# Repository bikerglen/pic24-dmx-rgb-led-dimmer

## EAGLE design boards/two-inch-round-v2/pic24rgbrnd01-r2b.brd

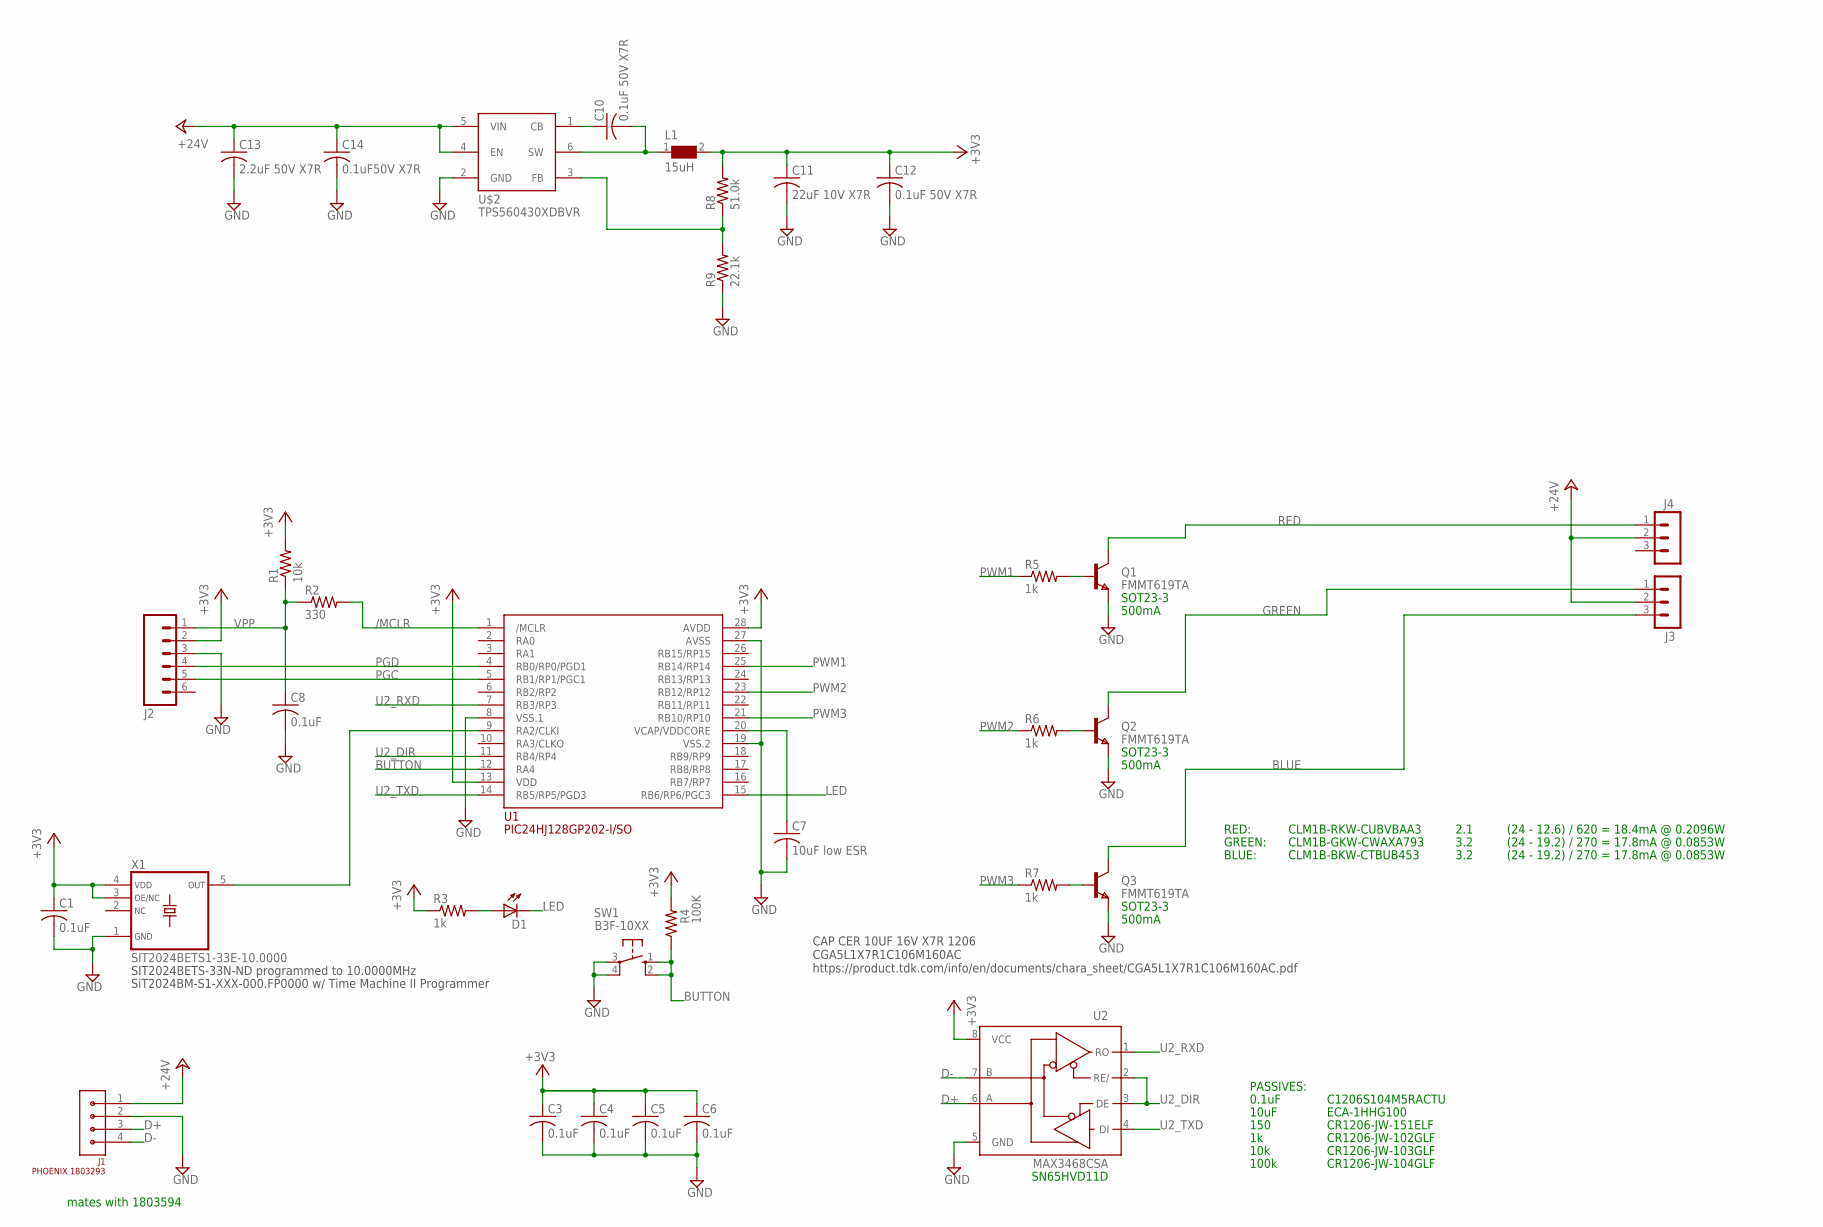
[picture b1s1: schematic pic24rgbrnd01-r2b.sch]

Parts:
C1, C3, C4, C5, C6, C8: 0.1uF; C0805
C7: 10uF low ESR; C1206
C10, C12: 0.1uF 50V X7R; C0805
C11: 22uF 10V X7R; C1206K; MFR_PART_NO C1206C226K8RAC7800
C13: 2.2uF 50V X7R; C1210K; MFR_PART_NO C1210C106K5RACTU
C14: 0.1uF50V X7R; C0805
D1: LED3MM
J1: PHOENIX 1803293; CON-PHOENIX-1803293-3.81-1X4
J2: M06SIP; 1X06
J3, J4: MA03-1
L1: 15uH; WE-SPC_48XX
Q1, Q2, Q3: FMMT619TA; SOT-23
R1: 10k; R0805
R2: 330; R0805
R3, R5, R6, R7: 1k; R0805
R4: 100K; R0805
R8: 51.0k; R0805
R9: 22.1k; R0805
SW1: B3F-10XX
U1: PIC24HJ128GP202-I/SO; SO28W
U2: MAX3468CSA; SO08
U$2: TPS560430XDBVR; SOT23-6
X1: SIT2024BETS1-33E-10.0000; SOT23-5

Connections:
+3V3: C1.1, C3.1, C4.1, C5.1, C6.1, C11.1, C12.1, J2.2, L1.2, R1.2, R3.1, R4.2, R8.2, U1.13 (VDD), U1.28 (AVDD), U2.8 (VCC), X1.3 (OE/NC), X1.4 (VDD)
+24V: C13.1, C14.1, J1.1, J3.2, J4.2, U$2.4 (EN), U$2.5 (VIN)
/MCLR: R2.2, U1.1 (/MCLR)
BLUE: J3.3, Q3.1 (C)
BUTTON: R4.1, SW1.1 (S), SW1.2 (S1), U1.12 (RA4)
CB: C10.1, U$2.1 (CB)
D+: J1.3, U2.6 (A)
D-: J1.4, U2.7 (B)
FB: R8.1, R9.2, U$2.3 (FB)
GND: C1.2, C3.2, C4.2, C5.2, C6.2, C7.2, C8.2, C11.2, C12.2, C13.2, C14.2, J1.2, J2.3, Q1.2 (E), Q2.2 (E), Q3.2 (E), R9.1, SW1.3, SW1.4 (P1), U1.8 (VSS.1), U1.19 (VSS.2), U1.27 (AVSS), U2.5 (GND), U$2.2 (GND), X1.1 (GND)
GREEN: J3.1, Q2.1 (C)
LED: D1.K (C), U1.15 (RB6/RP6/PGC3)
unnamed: C7.1, U1.20 (VCAP/VDDCORE)
unnamed: U1.9 (RA2/CLKI), X1.5 (OUT)
unnamed: Q1.3 (B), R5.2
unnamed: Q2.3 (B), R6.2
unnamed: Q3.3 (B), R7.2
unnamed: D1.A, R3.2
PGC: J2.5, U1.5 (RB1/RP1/PGC1)
PGD: J2.4, U1.4 (RB0/RP0/PGD1)
PWM1: R5.1, U1.25 (RB14/RP14)
PWM2: R6.1, U1.23 (RB12/RP12)
PWM3: R7.1, U1.21 (RB10/RP10)
RED: J4.1, Q1.1 (C)
SW: C10.2, L1.1, U$2.6 (SW)
U2_DIR: U1.11 (RB4/RP4), U2.2 (RE/), U2.3 (DE)
U2_RXD: U1.7 (RB3/RP3), U2.1 (RO)
U2_TXD: U1.14 (RB5/RP5/PGD3), U2.4 (DI)
VPP: C8.1, J2.1, R1.1, R2.1

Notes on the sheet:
SN65HVD11D
0.1uF
C1206S104M5RACTU
150
10k
100k
CR1206-JW-102GLF
CR1206-JW-151ELF
CR1206-JW-104GLF
CR1206-JW-103GLF
PASSIVES:
10uF
ECA-1HHG100
SOT23-3
500mA
RED:
CLM1B-RKW-CUBVBAA3
2.1
GREEN:
CLM1B-GKW-CWAXA793
3.2
BLUE:
CLM1B-BKW-CTBUB453
(24 - 12.6) / 620 = 18.4mA @ 0.2096W
(24 - 19.2) / 270 = 17.8mA @ 0.0853W
mates with 1803594
CAP CER 10UF 16V X7R 1206 CGA5L1X7R1C106M160AC https://product.tdk.com/info/en/documents/chara_sheet/CGA5L1X7R1C106M160AC.pdf
SIT2024BETS-33N-ND programmed to 10.0000MHz
SiT2024BM-S1-XXX-000.FP0000 w/ Time Machine II Programmer

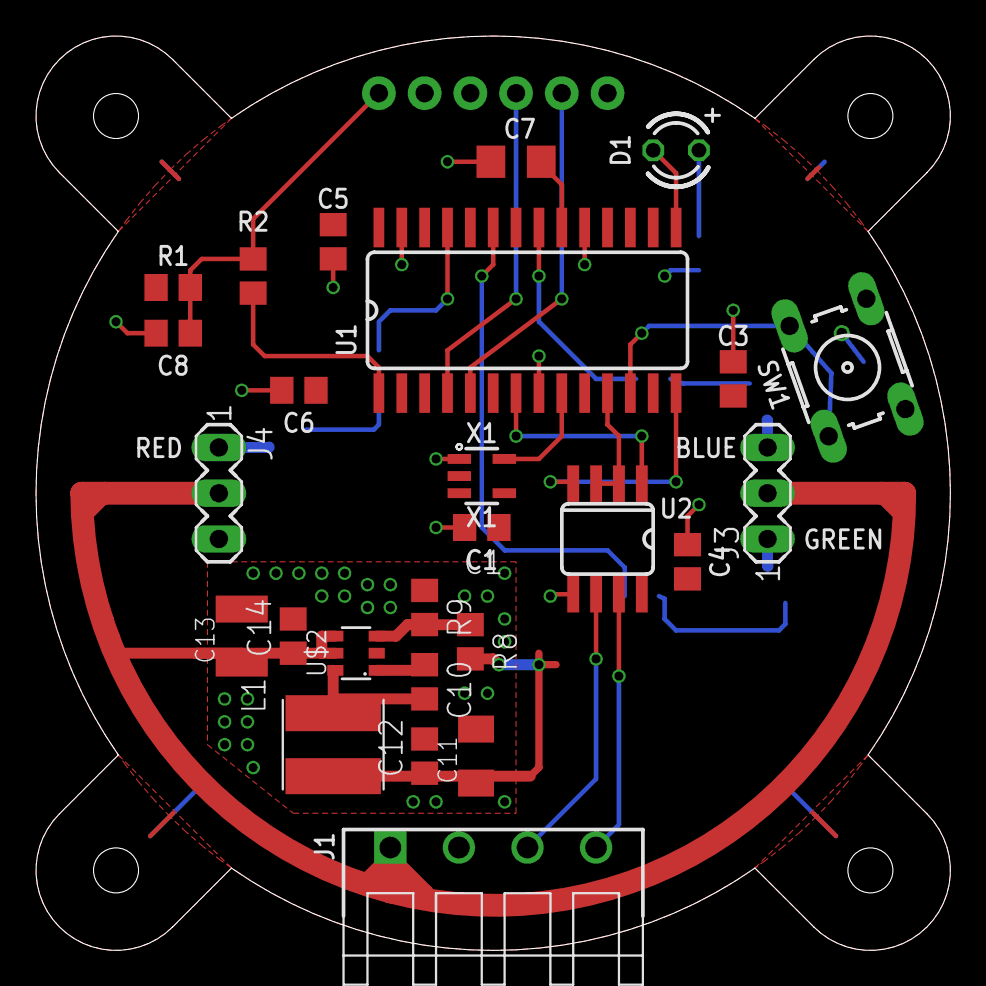
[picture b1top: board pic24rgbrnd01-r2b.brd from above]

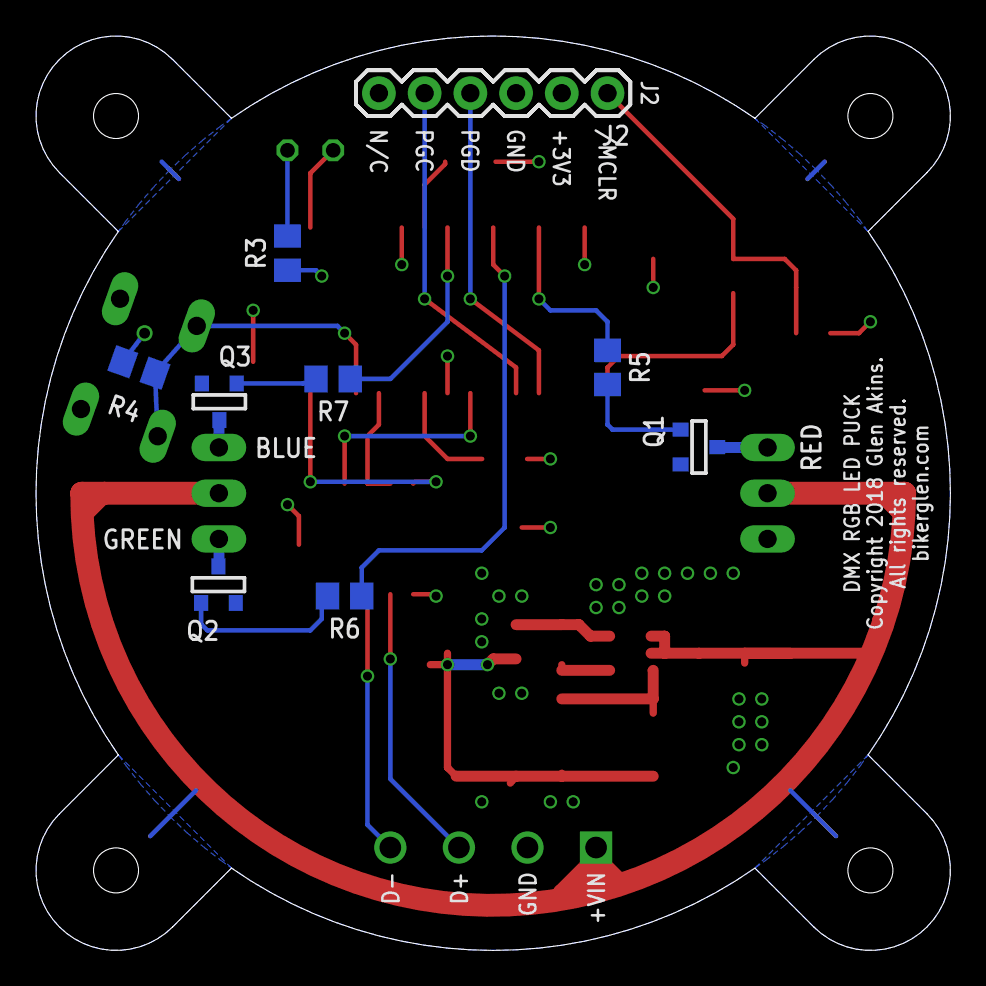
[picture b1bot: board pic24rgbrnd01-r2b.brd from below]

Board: 2 copper layers, 50.8 x 50.8 mm, 35 parts (9 on the bottom side), 29 nets.

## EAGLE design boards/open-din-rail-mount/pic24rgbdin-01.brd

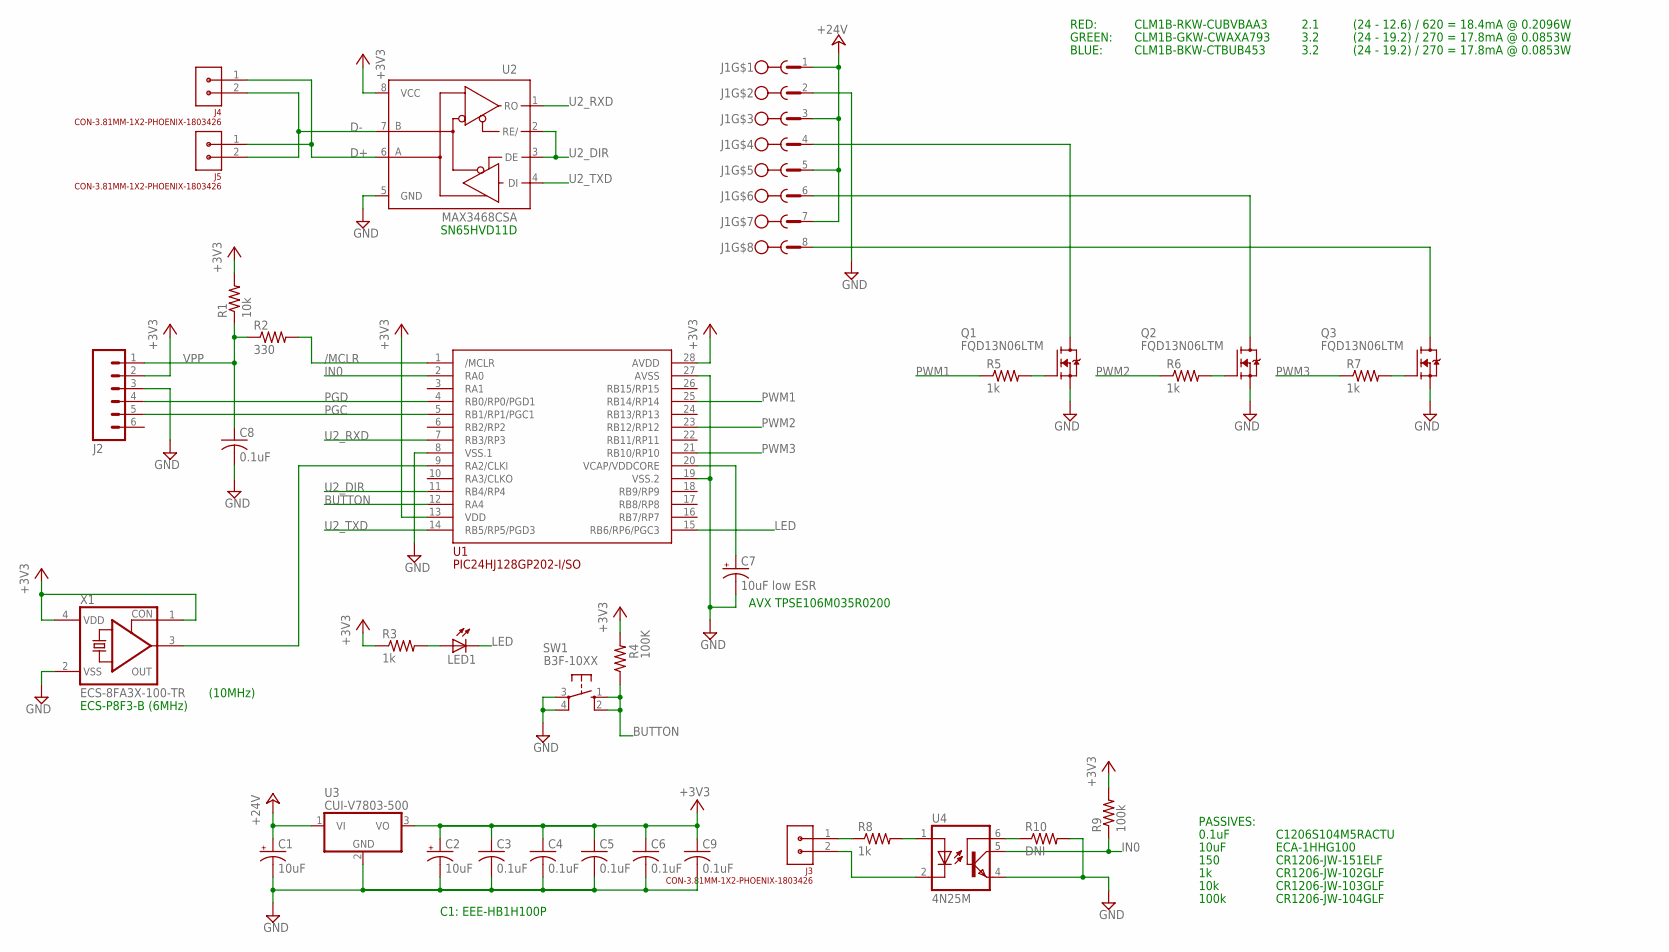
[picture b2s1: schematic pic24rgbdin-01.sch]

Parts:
C1, C2: 10uF; PANASONIC_D
C3, C4, C5, C6, C8, C9: 0.1uF; C1206
C7: 10uF low ESR; D/7343-31R
J1: CON-3.81MM-1X8-PHOENIX-HEADER-1803484; CON-PHOENIX-1803484-3.81-1X8
J2: M06SIP; 1X06
J3, J4, J5: CON-3.81MM-1X2-PHOENIX-1803426; CON-PHOENIX-1803426-3.81-1X2
LED1: LED3MM
Q1, Q2, Q3: FQD13N06LTM; TO252-D-PAK-FQD13N06LTM
R1: 10k; R1206
R2: 330; R1206
R3, R5, R6, R7, R8: 1k; R1206
R4: 100K; M1206
R9: 100k; R1206
R10: DNI; R1206
SW1: B3F-10XX
U1: PIC24HJ128GP202-I/SO; SO28W
U2: MAX3468CSA; SO08
U3: CUI-V7803-500; CUI-78XX-500
U4: 4N25M; DIL06
X1: ECS-8FA3X-100-TR; 1100S

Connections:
+3V3: C2.+, C3.1, C4.1, C5.1, C6.1, C9.1, J2.2, R1.2, R3.1, R4.2, R9.2, U1.13 (VDD), U1.28 (AVDD), U2.8 (VCC), U3.3 (VO), X1.1 (CON), X1.4 (VDD)
+24V: C1.+, J1.1, J1.3, J1.5, J1.7, U3.1 (VI)
/MCLR: R2.2, U1.1 (/MCLR)
BLUE: J1.8, Q3.P$4 (D)
BUTTON: R4.1, SW1.1 (S), SW1.2 (S1), U1.12 (RA4)
D+: J4.1, J5.1, U2.6 (A)
D-: J4.2, J5.2, U2.7 (B)
GND: C1.-, C2.-, C3.2, C4.2, C5.2, C6.2, C7.-, C8.2, C9.2, J1.2, J2.3, Q1.P$3 (S), Q2.P$3 (S), Q3.P$3 (S), R10.2, SW1.3, SW1.4 (P1), U1.8 (VSS.1), U1.19 (VSS.2), U1.27 (AVSS), U2.5 (GND), U3.2 (GND), U4.4 (EMI), X1.2 (VSS)
GREEN: J1.6, Q2.P$4 (D)
IN0: R9.1, U1.2 (RA0), U4.5 (COL)
LED: LED1.K (C), U1.15 (RB6/RP6/PGC3)
unnamed: Q2.P$1 (G), R6.2
unnamed: Q3.P$1 (G), R7.2
unnamed: R8.2, U4.1 (A)
unnamed: C7.+, U1.20 (VCAP/VDDCORE)
unnamed: U1.9 (RA2/CLKI), X1.3 (OUT)
unnamed: R10.1, U4.6 (BAS)
unnamed: J3.2, U4.2 (C)
unnamed: J3.1, R8.1
unnamed: Q1.P$1 (G), R5.2
unnamed: LED1.A, R3.2
PGC: J2.5, U1.5 (RB1/RP1/PGC1)
PGD: J2.4, U1.4 (RB0/RP0/PGD1)
PWM1: R5.1, U1.25 (RB14/RP14)
PWM2: R6.1, U1.23 (RB12/RP12)
PWM3: R7.1, U1.21 (RB10/RP10)
RED: J1.4, Q1.P$4 (D)
U2_DIR: U1.11 (RB4/RP4), U2.2 (RE/), U2.3 (DE)
U2_RXD: U1.7 (RB3/RP3), U2.1 (RO)
U2_TXD: U1.14 (RB5/RP5/PGD3), U2.4 (DI)
VPP: C8.1, J2.1, R1.1, R2.1

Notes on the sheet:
(10MHz)
ECS-P8F3-B (6MHz)
SN65HVD11D
C1: EEE-HB1H100P
0.1uF
C1206S104M5RACTU
150
10k
100k
CR1206-JW-102GLF
CR1206-JW-151ELF
CR1206-JW-104GLF
CR1206-JW-103GLF
PASSIVES:
10uF
ECA-1HHG100
RED:
CLM1B-RKW-CUBVBAA3
2.1
GREEN:
CLM1B-GKW-CWAXA793
3.2
BLUE:
CLM1B-BKW-CTBUB453
(24 - 12.6) / 620 = 18.4mA @ 0.2096W
(24 - 19.2) / 270 = 17.8mA @ 0.0853W
AVX TPSE106M035R0200

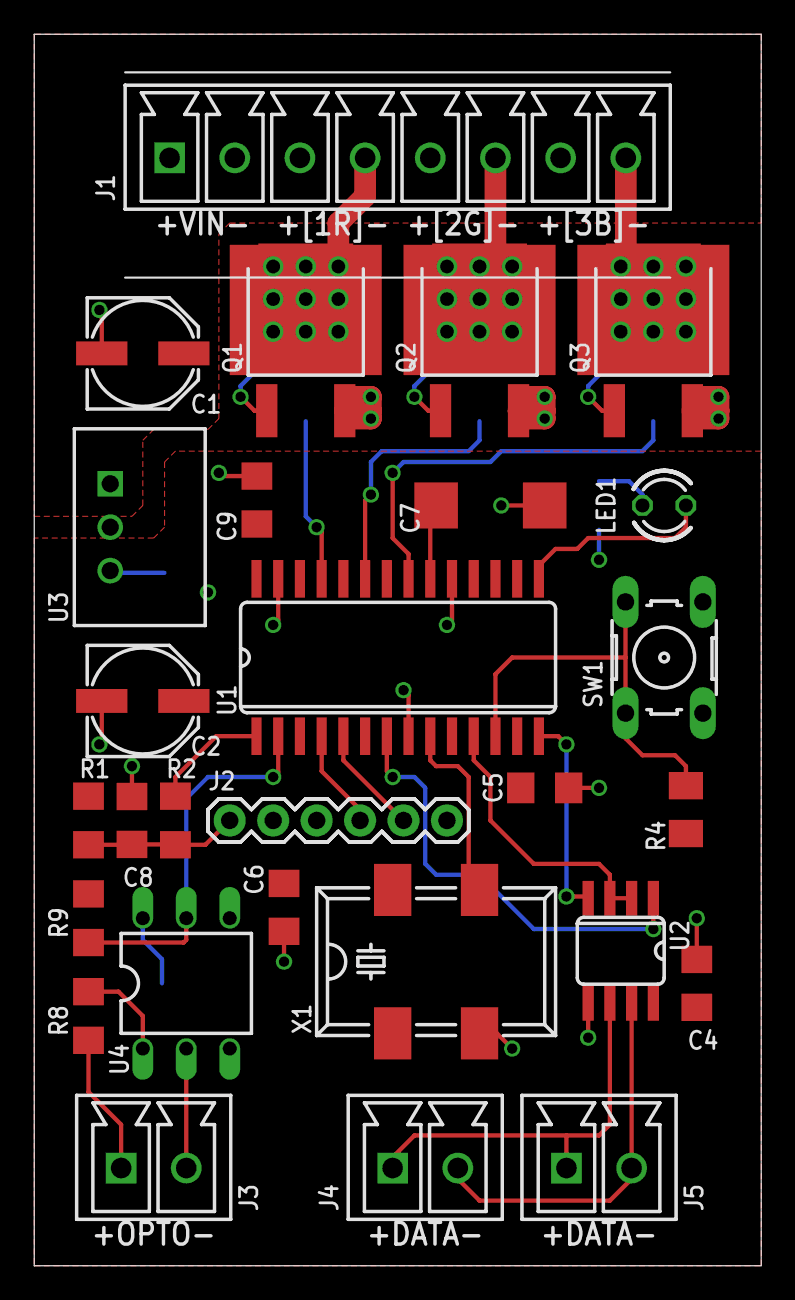
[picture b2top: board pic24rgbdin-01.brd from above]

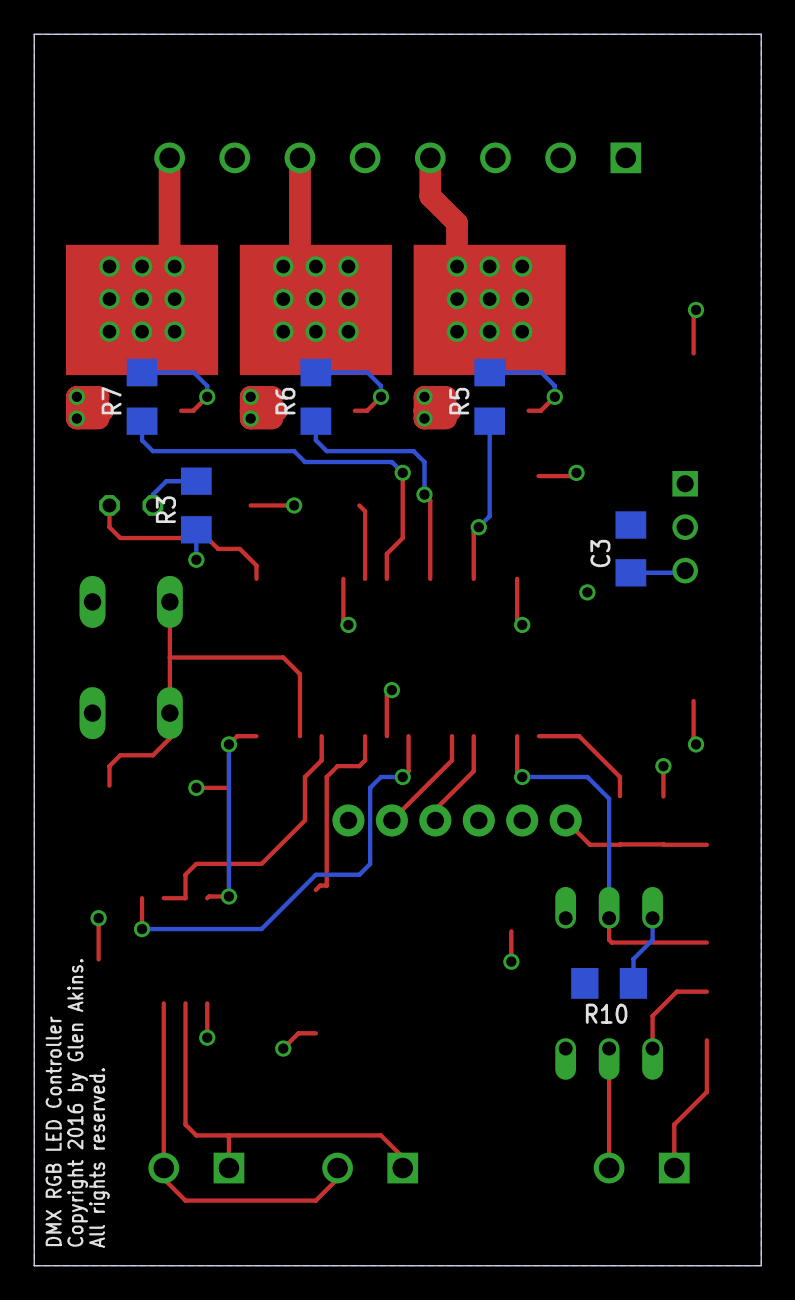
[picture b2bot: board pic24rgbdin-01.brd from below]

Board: 2 copper layers, 42.5 x 72.0 mm, 34 parts (6 on the bottom side), 31 nets.

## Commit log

2017-12-12 initial checkin
2019-03-25 added color wash
2019-03-25 initial checkin of v2 round boards

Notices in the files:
boards/open-din-rail-mount/pic24rgbdin-01.brd:
Copyright 2016 by Glen Akins.
All rights reserved.
boards/two-inch-round-v2/pic24rgbrnd01-r2b.brd:
Copyright 2018 Glen Akins.
parts and their libraries:
SparkFun-Connectors: Licensing: Creative Commons ShareAlike 4.0 International - https://creativecommons.org/licenses/by-sa/4.0
